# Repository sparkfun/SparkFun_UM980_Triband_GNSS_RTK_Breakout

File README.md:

SparkFun Triband GNSS RTK Breakout - UM980
===========================================================

[*SparkFun Triband GNSS RTK Breakout - UM980 (GPS-23286)*](https://www.sparkfun.com/products/23286)

The SparkFun Triband GNSS RTK Breakout features the UM980 GNSS high precision RTK position module from Unicore Communications. The UM980 is a 1408-Channel GNSS Receiver based on the Nebulas IV™ that is able to simultaneously track GPS L1/L2/L5, GLONASS L1/L2, Galileo E1/E5a/E5b/E6, Beidou B1I/B2I/B3I/B1C/B2a/B2b, QZSS L1/L2/L5, and SBAS. With this board, you will be able to know where your (or any object's) X, Y, and Z location is within roughly the width of your fingernail. When an RTK solution is reached, the module can achieve a horizontal accuracy of about 8mm (~0.3 inches) and vertical accuracy of 15mm (~0.59 inches). The UM980 is capable of both rover and base station operations.

We've included a rechargeable backup battery to keep the latest module configuration and satellite data available. This battery helps 'warm-start' the module, decreasing the time-to-first-fix dramatically. This module features a survey-in mode, allowing the module to become a base station and produce RTCM 3.x correction data. A SMA connector is included for a secure connection to a Triband GNSS antenna.

Currently, serial UART is only supported on the UM980 module. All three serial UART ports have been broken out to the USB-C connector via CH340, 4-pin locking JST connector, and BlueSMiRF header. Unique pins have also been broken out to the edge of the board. Various jumpers are also included to configure power and LEDs.

Repository Contents
-------------------

* **.github/workflows** - YAML files used for GitHub Actions and GitHub Pages/mkdocs
* **/Firmware** - UM980 Firmware packages
* **/Documents** - Datasheets and various documents related to the UM980
* **/Hardware** - Eagle files
* **/Software** - Related software for the UM980
* **/docs** - Online documentation files
  * **/assets** - Folder containing all the file assets used for product documentation
    * **/board_files** - Copy of design files used for product documentation
    * **/component_documentation** - Datasheets and manuals for hardware components
    * **/img** - Images for product documentation
  * **/github** - Files stating how to contribute and filing issues used for product documentation
  * **/javascript** - Folder containing custom javascript used for product documentation
  * **/stylesheet** - Folder containing CSS files used for product documentation
* **/overrides** - Customization files used for product documentation
  * **/.icons** - Icons used for GitHub used for product documentation
  * **./partials** - Used for product documentation

Documentation
--------------

* **[Installing an Arduino Library Guide](https://learn.sparkfun.com/tutorials/installing-an-arduino-library)** - Basic information on how to install an Arduino library.
* **[Library](https://github.com/sparkfun/SparkFun_Unicore_GNSS_Arduino_Library/)** - Unicore GNSS Arduino Library
* **[Hookup Guide](https://docs.sparkfun.com/SparkFun_UM980_Triband_GNSS_RTK_Breakout/)** - Hookup guide for the SparkFun Triband GNSS RTK Breakout - UM980.
* **[How to Update Firmware on a Unicore GNSS Receiver](https://docs.sparkfun.com/Update_Firmware_Unicore_GNSS_Receiver/introduction/)** - Tutorial on how to update firmware on a Unicore GNSS Receiver. This is a general tutorial that covers the RTK Torch and UM980 breakout. Note that this information also included in the SparkFun Triband GNSS RTK Breakout - UM980 Hookup Guide.

License Information
-------------------

This product is _**open source**_! 

Various bits of the code have different licenses applied. Anything SparkFun wrote is beerware; if you see me (or any other SparkFun employee) at the local, and you've found our code helpful, please buy us a round!

Please use, reuse, and modify these files as you see fit. Please maintain attribution to SparkFun Electronics and release anything derivative under the same license.

Distributed as-is; no warranty is given.

- Your friends at SparkFun.

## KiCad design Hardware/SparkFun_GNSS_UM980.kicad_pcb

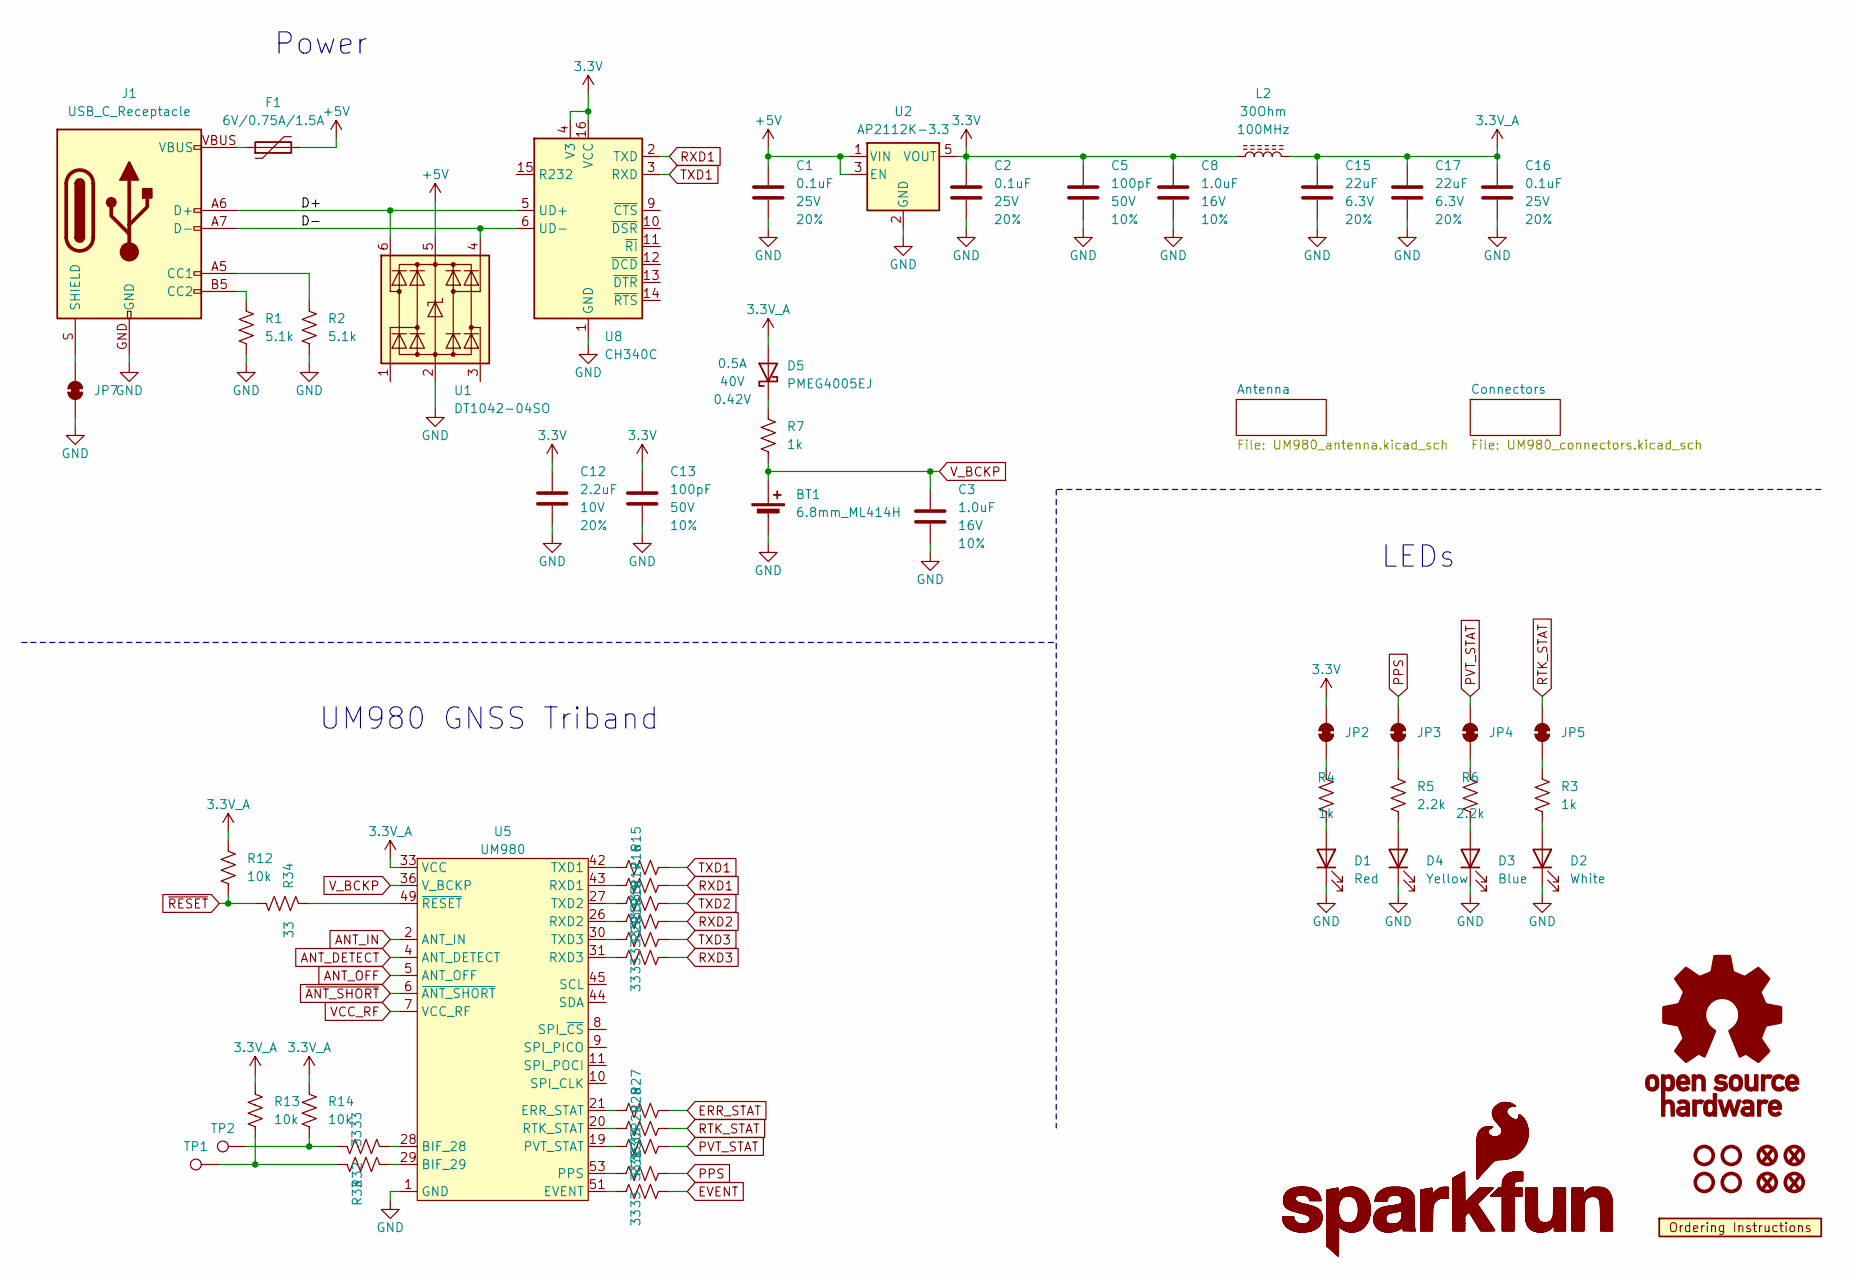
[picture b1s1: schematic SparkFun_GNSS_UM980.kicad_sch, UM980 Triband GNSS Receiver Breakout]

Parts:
BT1: 6.8mm_ML414H; ML414H_IV01E
C1, C2, C16: 0.1uF; C_0603_1608Metric; Voltage 25V; Tolerance 20%
C3, C8: 1.0uF; C_0603_1608Metric; Voltage 16V; Tolerance 10%
C5, C13: 100pF; C_0603_1608Metric; Voltage 50V; Tolerance 10%
C12: 2.2uF; C_0603_1608Metric; Voltage 10V; Tolerance 20%
C15, C17: 22uF; C_0603_1608Metric; Voltage 6.3V; Tolerance 20%
D1: Red; LED_0603_1608Metric_Red
D2: White; LED_0603_1608Metric_White
D3: Blue; LED_0603_1608Metric_Blue
D4: Yellow; LED_0603_1608Metric_Yellow
D5: PMEG4005EJ; SOD-323
F1: 6V/0.75A/1.5A; 1206
FID1, FID2, FID3, FID4: Fiducial_0.5mm; Fiducial_0.5mm_Mask1mm
G1: OSHW_Logo; Creative_Commons_License
G3: SparkFun_Logo
G5: SparkFun_Logo; SparkFun_Logo_8mm
J1: USB_C_Receptacle; USB-C_16
JP2, JP3, JP4, JP5, JP7: Jumper_2_NC_Trace
L2: 30Ohm; C_0603_1608Metric
R1, R2: 5.1k; R_0603_1608Metric
R3, R4, R7: 1k; R_0603_1608Metric
R5, R6: 2.2k; R_0603_1608Metric
R12, R13, R14: 10k; R_0603_1608Metric
R15, R16, R17, R18, R19, R20, R27, R28, R29, R30, R31, R32, R33, R34: 33; R_0603_1608Metric
ST1, ST2, ST3, ST4: Standoff
TP1, TP2: PTH; 1x01
U1: DT1042-04SO; SOT23-6
U2: AP2112K-3.3; SOT23-5
U5: UM980
U7: Ordering_Instructions
U8: CH340C; SO-16

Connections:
3.3V: C2.1, C5.1, C8.1, C12.1, C13.1, JP2.2 (B), L2.1, U2.5 (VOUT), U8.4 (V3), U8.16 (VCC); also elsewhere on the board
3.3V_A: C15.1, C16.1, C17.1, D5.A, L2.2, R12.1, R13.1, R14.1, U5.33 (VCC), U5.34 (VCC)
+5V: C1.1, F1.2, U1.5 (VCC), U2.1 (VIN), U2.3 (EN); also elsewhere on the board
/D+: J1.A6 (D+), J1.B6 (D+), U1.6 (I/O4), U8.5 (UD+)
/D-: J1.A7 (D-), J1.B7 (D-), U1.4 (I/O3), U8.6 (UD-)
ANT_DETECT: U5.4 (ANT_DETECT)
ANT_IN: U5.2 (ANT_IN); also elsewhere on the board
ANT_OFF: U5.5 (ANT_OFF)
ERR_STAT: R27.2; also elsewhere on the board
EVENT: R31.2; also elsewhere on the board
GND: BT1.-, C1.2, C2.2, C3.2, C5.2, C8.2, C12.2, C13.2, C15.2, C16.2, C17.2, D1.1 (K), D2.1 (K), D3.1 (K), D4.1 (K), J1.GND, JP7.1 (A), R1.2, R2.2, U1.2 (GND), U2.2 (GND), U5.1 (GND), U5.3 (GND), U5.12 (GND), U5.14 (GND), U5.32 (GND), U5.37 (GND), U5.41 (GND), U5.48 (GND), U5.55 (GND), U5.56 (GND), U5.57 (GND), U5.58 (GND), U5.59 (GND), U5.60 (GND), U5.61 (GND), U5.62 (GND), U5.63 (GND), U5.64 (GND), U5.65 (GND), U5.66 (GND), U5.67 (GND), U5.68 (GND), U5.69 (GND), U5.70 (GND), U5.71 (GND), U5.72 (GND), U5.73 (GND), U5.74 (GND), U5.75 (GND), U5.76 (GND), U5.77 (GND), U5.78 (GND), U5.79 (GND), U5.80 (GND), U5.81 (GND), U5.82 (GND), U5.83 (GND), U5.84 (GND), U5.85 (GND), U5.86 (GND), U5.87 (GND), U5.88 (GND), U5.89 (GND), U5.90 (GND), U5.91 (GND), U5.92 (GND), U5.93 (GND), U5.94 (GND), U5.95 (GND), U5.96 (GND), U5.97 (GND), U5.98 (GND), U5.99 (GND), U5.100 (GND), U5.101 (GND), U5.102 (GND), U8.1 (GND); also elsewhere on the board
unnamed: D1.2 (A), R4.2
unnamed: D2.2 (A), R3.2
unnamed: D3.2 (A), R6.2
unnamed: D4.2 (A), R5.2
unnamed: D5.C, R7.1
unnamed: F1.1, J1.VBUS
unnamed: J1.A5 (CC1), R2.1
unnamed: J1.B5 (CC2), R1.1
unnamed: J1.S (SHIELD), JP7.2 (B)
unnamed: JP2.1 (A), R4.1
unnamed: JP3.1 (A), R5.1
unnamed: JP4.1 (A), R6.1
unnamed: JP5.1 (A), R3.1
unnamed: R13.2, R33.1, TP1.1
unnamed: R14.2, R32.1, TP2.1
unnamed: R32.2, U5.28 (BIF_28)
unnamed: R33.2, U5.29 (BIF_29)
unnamed: R27.1, U5.21 (ERR_STAT)
unnamed: R31.1, U5.51 (EVENT)
unnamed: R30.1, U5.53 (PPS)
unnamed: R29.1, U5.19 (PVT_STAT)
unnamed: R28.1, U5.20 (RTK_STAT)
unnamed: R16.1, U5.43 (RXD1)
unnamed: R18.1, U5.26 (RXD2)
unnamed: R20.1, U5.31 (RXD3)
unnamed: R15.1, U5.42 (TXD1)
unnamed: R17.1, U5.27 (TXD2)
unnamed: R19.1, U5.30 (TXD3)
unnamed: R34.1, U5.49 (~RESET)
PPS: JP3.2 (B), R30.2; also elsewhere on the board
PVT_STAT: JP4.2 (B), R29.2; also elsewhere on the board
RTK_STAT: JP5.2 (B), R28.2; also elsewhere on the board
RXD1: R16.2, U8.2 (TXD)
RXD2: R18.2; also elsewhere on the board
RXD3: R20.2; also elsewhere on the board
TXD1: R15.2, U8.3 (RXD)
TXD2: R17.2; also elsewhere on the board
TXD3: R19.2; also elsewhere on the board
VCC_RF: U5.7 (VCC_RF); also elsewhere on the board
V_BCKP: BT1.+, C3.1, R7.2, U5.36 (V_BCKP)
~ANT_SHORT: U5.6 (~ANT_SHORT)
~RESET: R12.2, R34.2; also elsewhere on the board

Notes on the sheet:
LEDs
UM980 GNSS Triband
Power

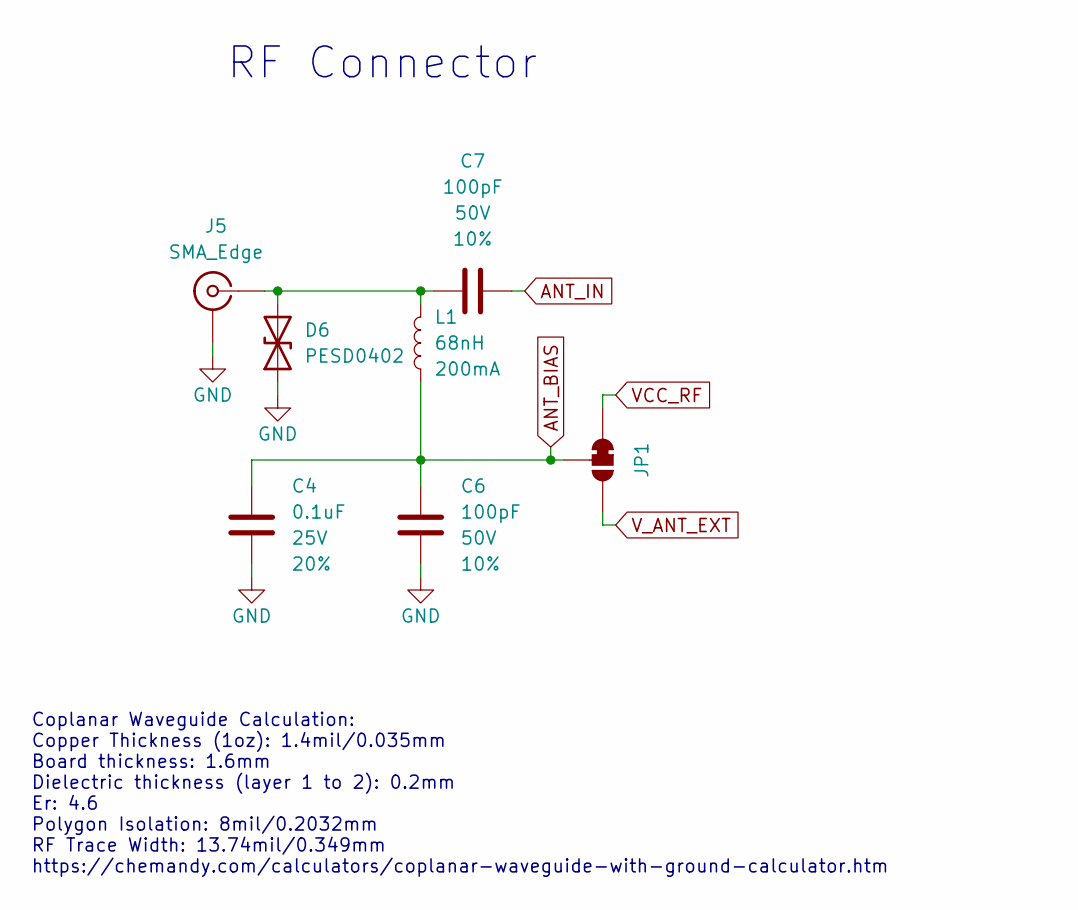
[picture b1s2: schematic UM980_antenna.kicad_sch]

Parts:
C4: 0.1uF; C_0603_1608Metric; Voltage 25V; Tolerance 20%
C6, C7: 100pF; C_0603_1608Metric; Voltage 50V; Tolerance 10%
D6: PESD0402; C_0402_1005Metric
J5: SMA_Edge
JP1: Jumper_3_NC-1_Trace
L1: 68nH; C_0402_1005Metric

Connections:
ANT_BIAS: C4.1, C6.1, JP1.2 (C), L1.1
ANT_IN: C7.2; also elsewhere on the board
GND: C4.2, C6.2, D6.1 (A1), J5.2 (Ext); also elsewhere on the board
unnamed: C7.1, D6.2 (A2), J5.1 (In), L1.2
VCC_RF: JP1.1 (A); also elsewhere on the board
V_ANT_EXT: JP1.3 (B); also elsewhere on the board

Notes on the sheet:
Coplanar Waveguide Calculation: Copper Thickness (1oz): 1.4mil/0.035mm Board thickness: 1.6mm Dielectric thickness (layer 1 to 2): 0.2mm Er: 4.6 Polygon Isolation: 8mil/0.2032mm RF Trace Width: 13.74mil/0.349mm https://chemandy.com/calculators/coplanar-waveguide-with-ground-calculator.htm
RF Connector

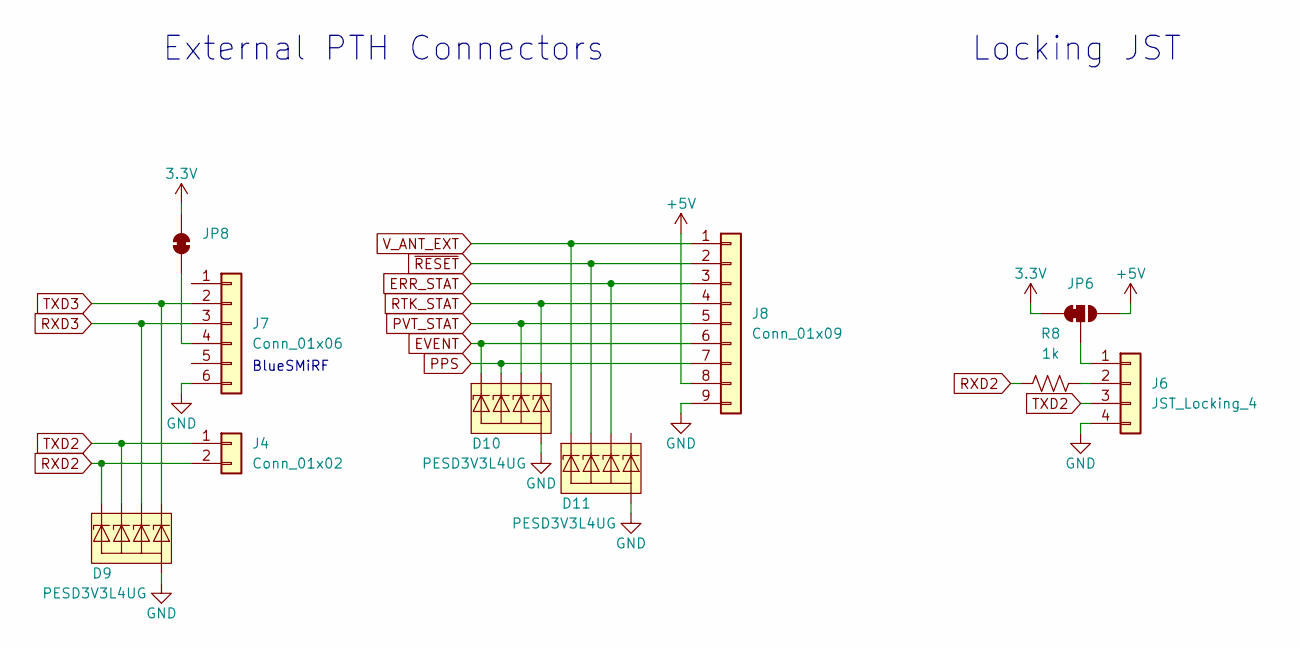
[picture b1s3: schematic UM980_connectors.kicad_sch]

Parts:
D9, D10, D11: PESD3V3L4UG; SOT-353
J4: Conn_01x02; 1x02
J6: JST_Locking_4; JST_SMD_1.25mm-4_Locking
J7: Conn_01x06; 1x06
J8: Conn_01x09; 1x09
JP6: Jumper_3_NC-1_Trace
JP8: Jumper_2_NC_Trace
R8: 1k; R_0603_1608Metric

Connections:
3.3V: JP6.1 (A), JP8.2 (B); also elsewhere on the board
+5V: J8.8, JP6.3 (B); also elsewhere on the board
ERR_STAT: D11.4 (K3), J8.3; also elsewhere on the board
EVENT: D10.1 (K1), J8.6; also elsewhere on the board
GND: D9.2 (A), D10.2 (A), D11.2 (A), J6.4, J7.6, J8.9; also elsewhere on the board
unnamed: J6.1, JP6.2 (C)
unnamed: J6.2, R8.2
unnamed: J7.4, JP8.1 (A)
PPS: D10.3 (K2), J8.7; also elsewhere on the board
PVT_STAT: D10.4 (K3), J8.5; also elsewhere on the board
RTK_STAT: D10.5 (K4), J8.4; also elsewhere on the board
RXD2: D9.1 (K1), J4.2, R8.1; also elsewhere on the board
RXD3: D9.4 (K3), J7.3; also elsewhere on the board
TXD2: D9.3 (K2), J4.1, J6.3; also elsewhere on the board
TXD3: D9.5 (K4), J7.2; also elsewhere on the board
V_ANT_EXT: D11.1 (K1), J8.1; also elsewhere on the board
~RESET: D11.3 (K2), J8.2; also elsewhere on the board

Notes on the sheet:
Locking JST
External PTH Connectors
BlueSMiRF

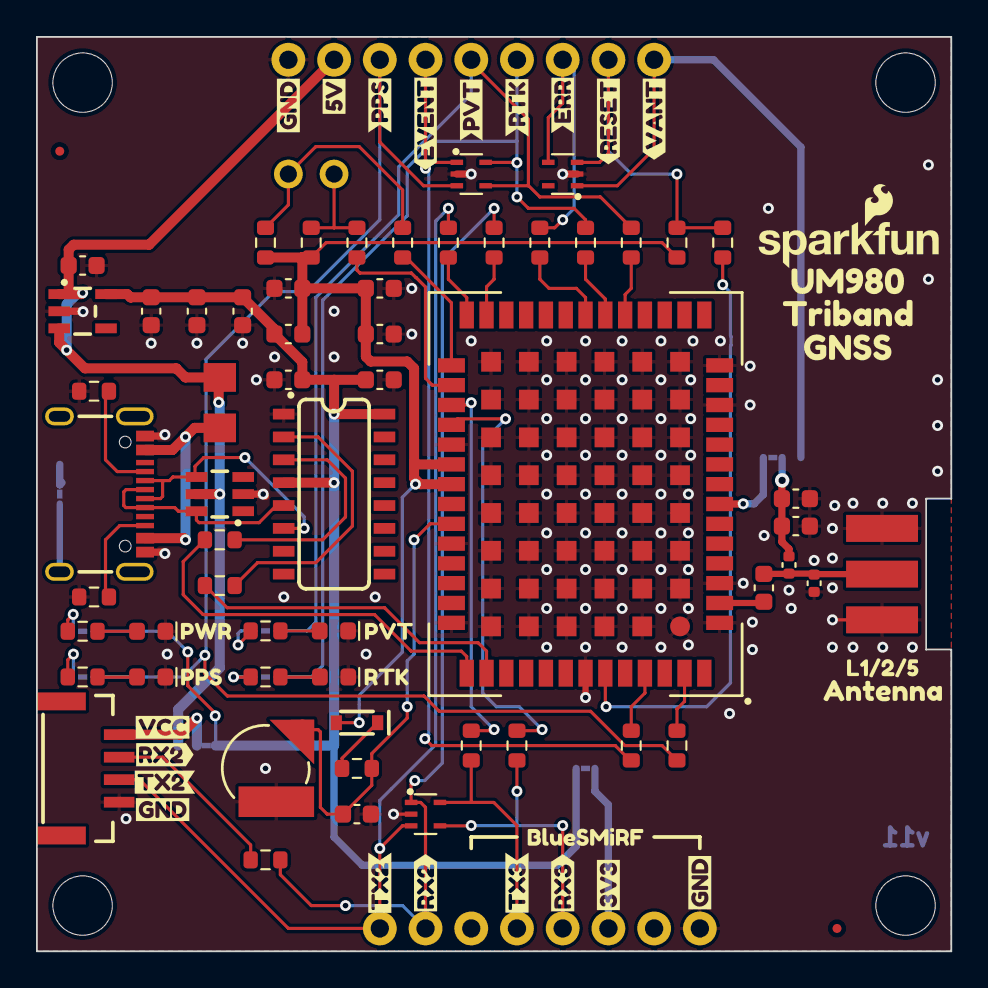
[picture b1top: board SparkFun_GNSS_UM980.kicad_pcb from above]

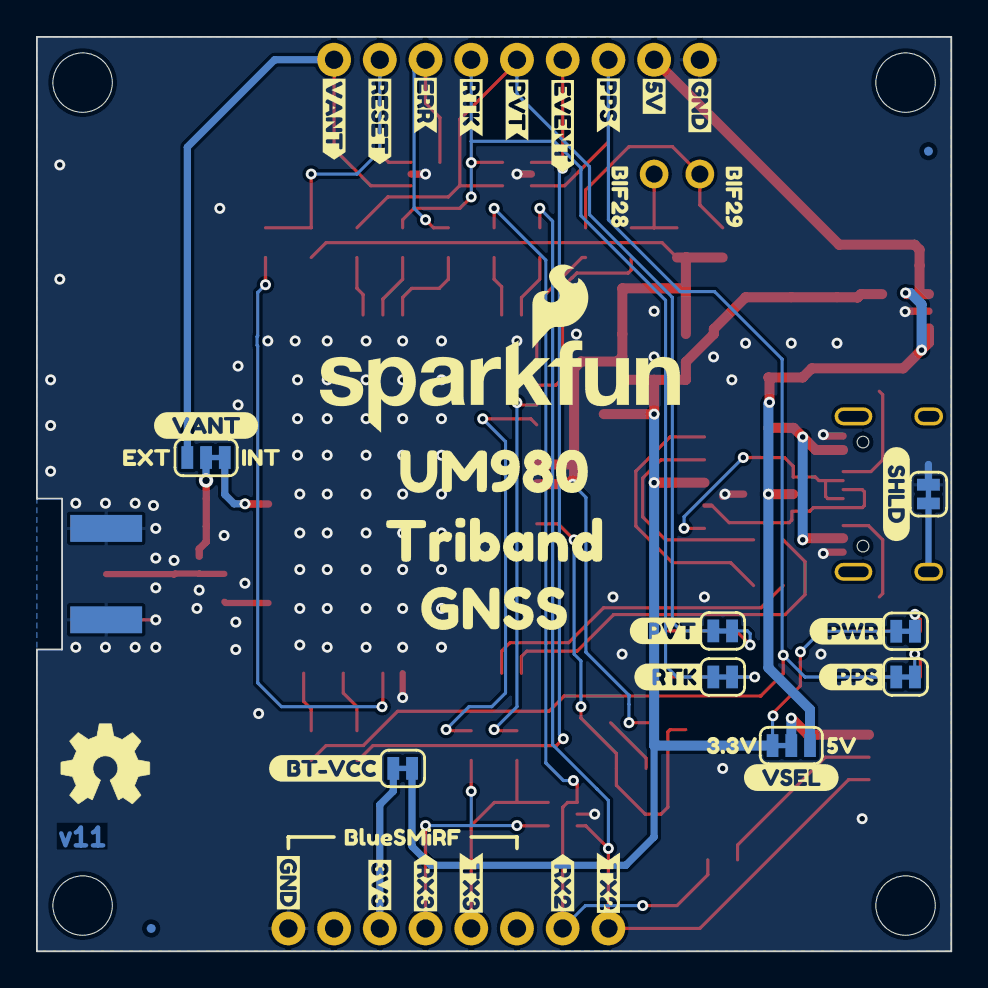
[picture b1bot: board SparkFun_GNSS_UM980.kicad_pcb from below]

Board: 4 copper layers, 50.8 x 50.8 mm, 144 parts (44 on the bottom side), 56 nets.

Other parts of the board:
Ref**: Val**; OSHW_Logo_5mm
kibuzzard-64C2E6A3: G***; kibuzzard-64C2E6A3
kibuzzard-64C2E6BD: G***; kibuzzard-64C2E6BD
kibuzzard-64C2E6C9: G***; kibuzzard-64C2E6C9
kibuzzard-64C2E6D6: G***; kibuzzard-64C2E6D6
kibuzzard-64C2E9A2: G***; kibuzzard-64C2E9A2
kibuzzard-64C2E77C: G***; kibuzzard-64C2E77C
kibuzzard-64C2E728: G***; kibuzzard-64C2E728
kibuzzard-64C2EADB: G***; kibuzzard-64C2EADB
kibuzzard-64C2EAF0: G***; kibuzzard-64C2EAF0
kibuzzard-64C2EB11: G***; kibuzzard-64C2EB11
kibuzzard-64C2EB16: G***; kibuzzard-64C2EB16
kibuzzard-64C3DF93: G***; kibuzzard-64C3DF93
kibuzzard-64C41486: G***; kibuzzard-64C41486
kibuzzard-64CB1646: G***; kibuzzard-64CB1646
kibuzzard-64CB1658: G***; kibuzzard-64CB1658
kibuzzard-64D296A7: G***; kibuzzard-64D296A7
kibuzzard-64D296AE: G***; kibuzzard-64D296AE
kibuzzard-64D2969C: G***; kibuzzard-64D2969C
kibuzzard-64E773DA: G***; kibuzzard-64E773DA
kibuzzard-64E773E5: G***; kibuzzard-64E773E5
kibuzzard-64E774A4: G***; kibuzzard-64E774A4
kibuzzard-64E774AA: G***; kibuzzard-64E774AA
kibuzzard-64E774B1: G***; kibuzzard-64E774B1
kibuzzard-64E774B8: G***; kibuzzard-64E774B8
kibuzzard-64E774C0: G***; kibuzzard-64E774C0
kibuzzard-64E774C8: G***; kibuzzard-64E774C8
kibuzzard-64E774E1: G***; kibuzzard-64E774E1
kibuzzard-64E774E7: G***; kibuzzard-64E774E7
kibuzzard-64E774EF: G***; kibuzzard-64E774EF
kibuzzard-64E774F5: G***; kibuzzard-64E774F5
kibuzzard-64E774FC: G***; kibuzzard-64E774FC
kibuzzard-64E7749D: G***; kibuzzard-64E7749D
kibuzzard-64E7750F: G***; kibuzzard-64E7750F
kibuzzard-64E7751D: G***; kibuzzard-64E7751D
kibuzzard-64E7752B: G***; kibuzzard-64E7752B
kibuzzard-64E7753A: G***; kibuzzard-64E7753A
kibuzzard-64E7754F: G***; kibuzzard-64E7754F
kibuzzard-64E77494: G***; kibuzzard-64E77494
kibuzzard-64E77501: G***; kibuzzard-64E77501
kibuzzard-64E77509: G***; kibuzzard-64E77509
kibuzzard-64E77517: G***; kibuzzard-64E77517
kibuzzard-64E77524: G***; kibuzzard-64E77524
kibuzzard-64E77534: G***; kibuzzard-64E77534
kibuzzard-64E77542: G***; kibuzzard-64E77542
kibuzzard-64E77548: G***; kibuzzard-64E77548
kibuzzard-64E77555: G***; kibuzzard-64E77555
kibuzzard-64ED068F: G***; kibuzzard-64ED068F
kibuzzard-64ED0510: G***; kibuzzard-64ED0510
kibuzzard-64ED0536: G***; kibuzzard-64ED0536
kibuzzard-64ED0547: G***; kibuzzard-64ED0547
kibuzzard-64ED0553: G***; kibuzzard-64ED0553
kibuzzard-64ED0645: G***; kibuzzard-64ED0645
kibuzzard-64ED0652: G***; kibuzzard-64ED0652
kibuzzard-64ED0681: G***; kibuzzard-64ED0681
kibuzzard-6501FDDA, kibuzzard-6501FDDA#2: G***; kibuzzard-6501FDDA
kibuzzard-650880D6: G***; kibuzzard-650880D6
kibuzzard-650880DF: G***; kibuzzard-650880DF
kibuzzard-650880E6: G***; kibuzzard-650880E6
kibuzzard-650885D8: G***; kibuzzard-650885D8
kibuzzard-65087150: G***; kibuzzard-65087150
kibuzzard-65087158: G***; kibuzzard-65087158

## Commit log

2023-07-28 Remove backups
2023-07-28 Ignore cache
2023-07-28 Remove old files
2023-07-31 Add silk. Remove linked logos in sch.
2023-08-10 Update PDFs
2023-08-10 Update panel files
2023-08-10 Update design with PROD_IDs
2023-09-13 Change port 3 to be compatible with BlueSMiRF
2023-09-18 Post design review.
2023-10-04 Add updated firmware and UPrecise executable
2023-12-14 Pushing Hookup Guide for Launch
2023-12-14 Remove Site from Force Pushing to GitHub Pages
2023-12-14 Update mkdocs.yml
    With Python 3.12, the use of `distutils` in merger.py creates an error. Adding `setuptools` module as a workaround.
2023-12-14 Linking Product Showcase
2023-12-18 Update Product Showcase Link
2023-12-21 Update Cable to Longer Version
2023-12-21 Deployed fa44d5d with MkDocs version: 1.5.3
2024-06-26 Update Software and Firmware Links
2024-06-26 Update Images and Version Number
2024-06-28 Fix typos
2024-07-01 Breakout Verification to New Page, Remove Hide from Grid Cards
2024-07-01 Deployed bb55e78 with MkDocs version: 1.6.0
2024-08-19 Deployed c6be45b with MkDocs version: 1.6.0
2024-08-19 Update to v8. Update models.
2024-10-28 Add cookies
2024-10-29 Deployed 20190f8 with MkDocs version: 1.6.1
2024-11-14 Add 3D Models
2024-11-15 Remove STL FIle
2024-12-06 Update SparkFun_GNSS_UM980_v11.zip
    - Update zipped KiCad Files for 3D Models
2024-12-06 Deployed 2ffa4cb with MkDocs version: 1.6.1
2025-02-20 Update introduction.md
    Fixing missing images
2026-06-03 Deployed 13c0f45 with MkDocs version: 1.6.1

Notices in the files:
parts and their libraries:
Released under the Creative Commons Attribution Share-Alike 4.0 License
https://creativecommons.org/licenses/by-sa/4.0
